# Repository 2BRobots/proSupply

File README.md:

# proSupply

This is the ultimate power supply for your breadboard! It can give you a regulated 5v, 3.3v and 1.8v output from a USB port or charger.

What is it?

This is a power supply designed to be used in a breadboard for develop and test digital logic circuits. It has 5v, 3.3v and 1.8v outputs that makes it great for this purpose. It is powered via a micro usb connector so you can attach it your PC, phone charger or power bank. Also it has an external Vin pin, it is protected from inverse polarization, overvoltage and undervoltage. All the pins feature a overcurrent and overheating shutdown so you don't need to worry about burning your computer's USB port by a short circuit.

Why did you make it?

I make it to work with circuits in my breadboard on the go and without worry for a bad connection or overcurrent.

What makes it special?

It has a unregulated Vout pin, regulated 5v, 3.3v and 1.8v. Also it has an external Vin pin so you can power it without using the micro usb port. Regulated voltage can give up to 250ma per channel and the power supply can give up to 750ma in total before the protection circuit starts pulsing the output and the red led blinks indicating a fault condition. Also when using Vin pin the protector circuits shuts down everything is the voltage is to high in order to prevent damage, it does the same in undervoltage for prevent malfunction. This boards are manufactured by me using a DIY reflow oven, each purchase helps me to continue doing more projects and materializing ideas.

Everything is open source so you can check the schematics and eagle board files. Available in this repo. 

<iframe width="815" height="568" src="https://www.youtube.com/embed/M1XWo04UHaw" frameborder="0" allowfullscreen></iframe>

=========================================================================================================================================
DAFR Electronics invest time and resources in making this content. If you valorate our hard work please buy from us our products or donate. This work is shared under creative commons license BY-NC-SA. 

Thanks :)

=========================================================================================================================================

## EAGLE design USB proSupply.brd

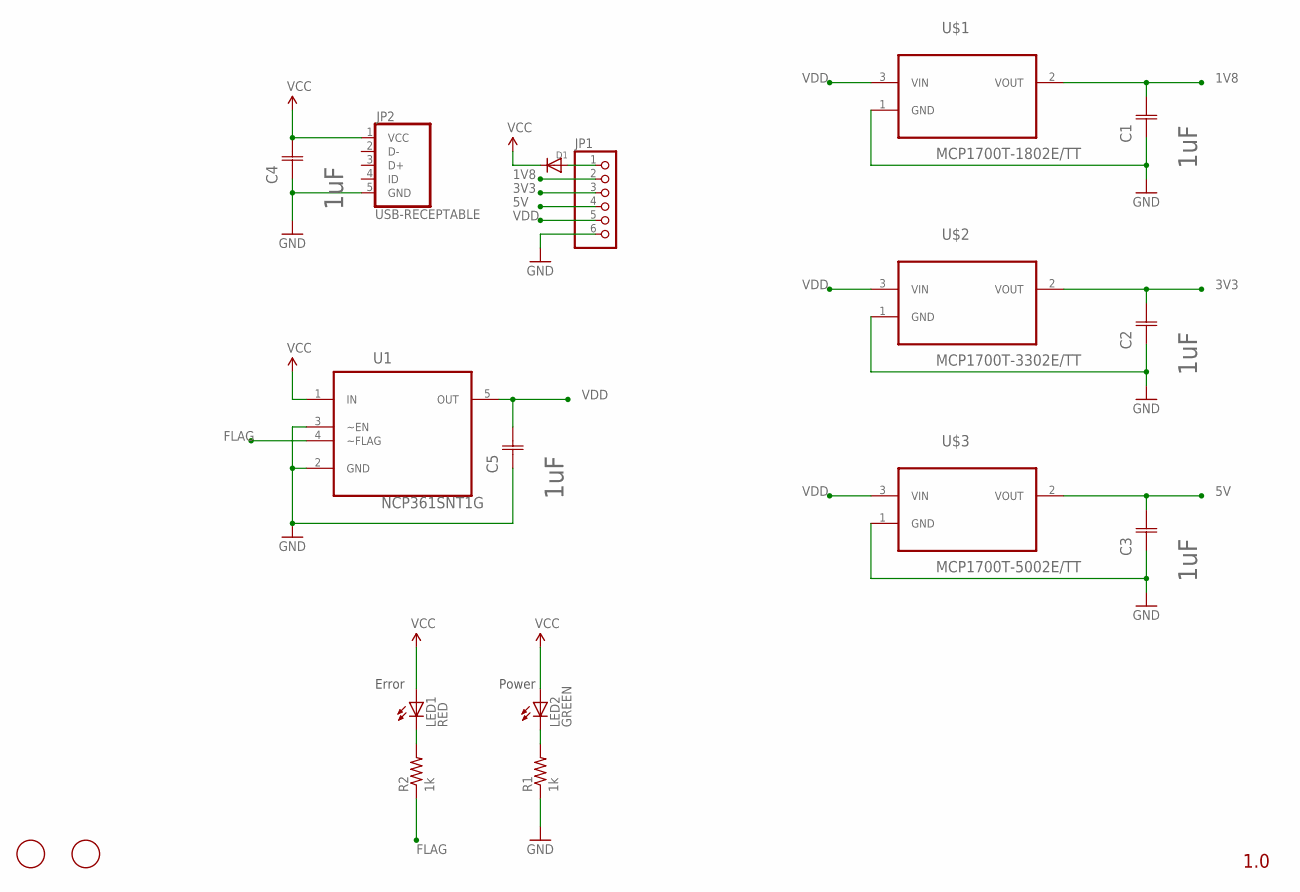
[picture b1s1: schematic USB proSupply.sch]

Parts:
C1, C2, C3, C4, C5: 1uF; CAPC1608X94N
D1: DIODESOD-123; SOD-123
JP1: PINHD-1X6; 1X06
JP2: USB-RECEPTABLE; FCI-10103594-0001LF
LED1: RED; CHIPLED_1206
LED2: GREEN; CHIPLED_1206
R1, R2: 1k; 0805
U1: NCP361SNT1G; SOP95P275X110-5N
U$1: MCP1700T-1802E/TT; SOT95P237X112-3N
U$2: MCP1700T-3302E/TT; SOT95P237X112-3N
U$3: MCP1700T-5002E/TT; SOT95P237X112-3N
U$5, U$6: FIDUCIAL; FIDUCIAL_1MM

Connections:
1V8: C1.2 (C2), JP1.2, U$1.2 (VOUT)
3V3: C2.2 (C2), JP1.3, U$2.2 (VOUT)
5V: C3.2 (C2), JP1.4, U$3.2 (VOUT)
FLAG: R2.1, U1.4 (~FLAG)
GND: C1.1 (C1), C2.1 (C1), C3.1 (C1), C4.1 (C1), C5.1 (C1), JP1.6, JP2.5 (GND), R1.1, U1.2 (GND), U1.3 (~EN), U$1.1 (GND), U$2.1 (GND), U$3.1 (GND)
unnamed: D1.A, JP1.1
unnamed: LED1.C, R2.2
unnamed: LED2.C, R1.2
VCC: C4.2 (C2), D1.C, JP2.1 (VCC), LED1.A, LED2.A, U1.1 (IN)
VDD: C5.2 (C2), JP1.5, U1.5 (OUT), U$1.3 (VIN), U$2.3 (VIN), U$3.3 (VIN)

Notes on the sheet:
1.0
Error
Power

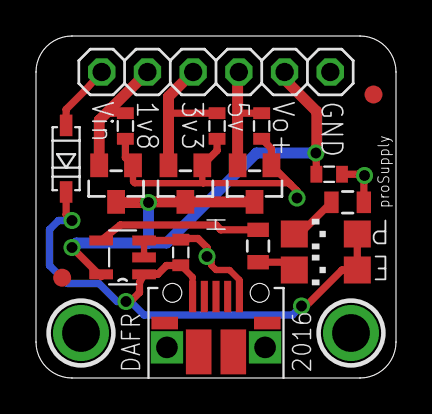
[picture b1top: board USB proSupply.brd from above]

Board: 2 copper layers, 20.0 x 19.0 mm, 18 parts (0 on the bottom side), 10 nets.

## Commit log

2016-07-19 Publishing v1 of the boards
    Note: USB connector footprint must be fixed for better grip.

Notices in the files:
USB proSupply.brd:
CC-BY-SA
parts and their libraries:
SparkFun-Resistors: Licensing: Creative Commons ShareAlike 4.0 International - https://creativecommons.org/licenses/by-sa/4.0
